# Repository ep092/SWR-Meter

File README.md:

# SWR-Meter
The goal is a SWR-Meter to analyse Antennas from 2,4GHz to 5,8GHz e.g. for FPV-Antennas.
The module ist based on a directional coupler and a power detector. 
A uC reads in the voltage with it's ADC and shows the results.

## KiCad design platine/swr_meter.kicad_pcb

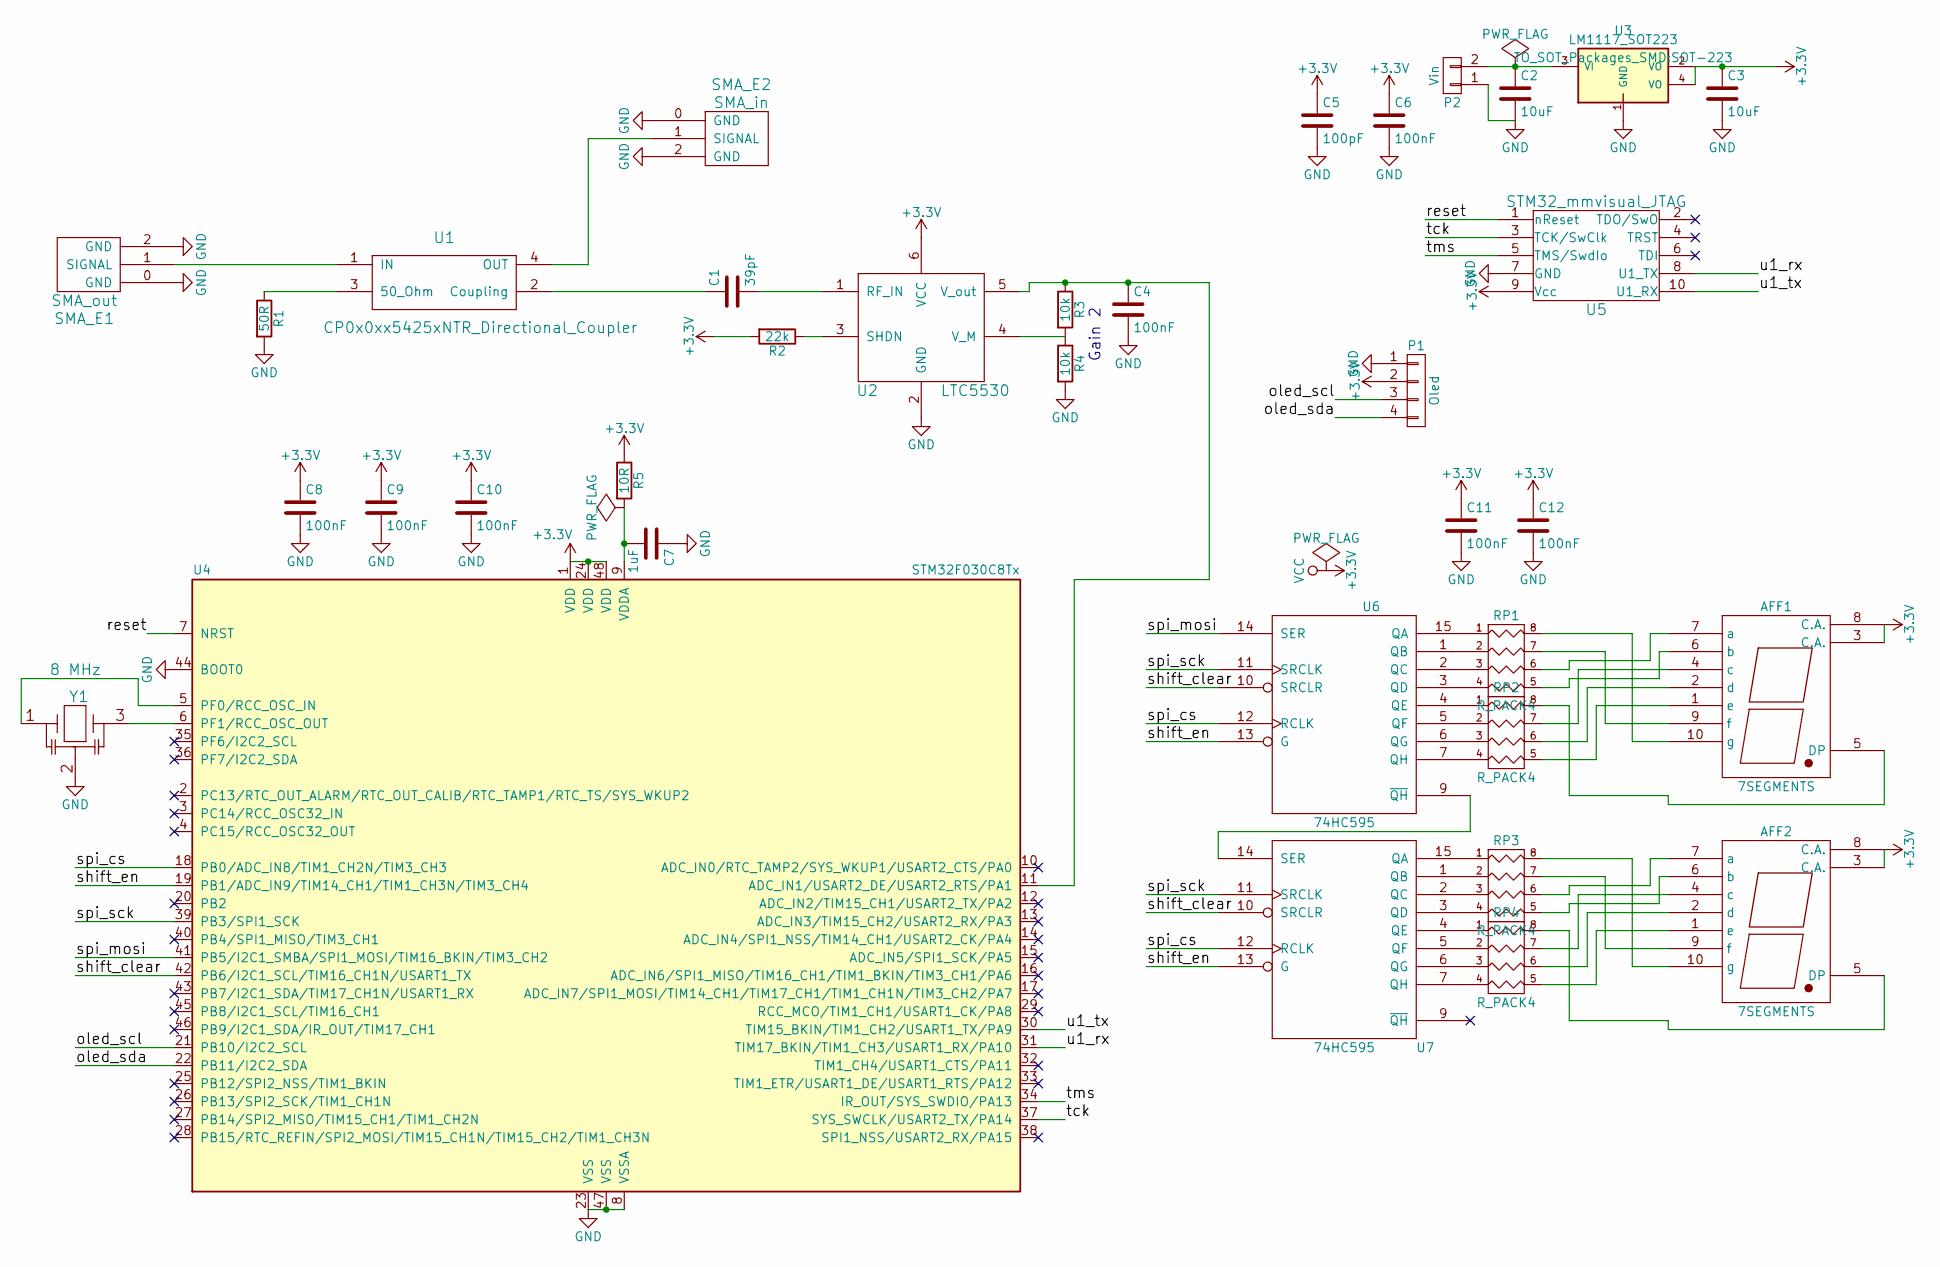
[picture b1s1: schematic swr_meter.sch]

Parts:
AFF1, AFF2: 7SEGMENTS; DIP-10_W7.62mm
C1: 39pF; C_0603
C2, C3: 10uF; R_0805
C4, C6, C8, C9, C10, C11, C12: 100nF; R_0402
C5: 100pF; C_0603
C7: 1uF; C_0603
P1: Oled; Pin_Header_Straight_1x04
P2: Vin; Pin_Header_Straight_1x02
R1: 50R; R_0603
R2: 22k; R_0603
R3, R4: 10k; R_0603
R5: 10R; C_0603
RP1, RP2, RP3, RP4: R_PACK4; R_array_4
SMA_E1: SMA_out; SMA_EDGE_Johnson_142-0701-801
SMA_E2: SMA_in; SMA_EDGE_Johnson_142-0701-801
U1: CP0x0xx5425xNTR_Directional_Coupler; CP0603_directional_coupler
U2: LTC5530; SOT-23-6
U3: LM1117_SOT223; SOT-223
U4: STM32F030C8Tx; LQFP-48_7x7mm_Pitch0.5mm
U5: STM32_mmvisual_JTAG; MICROMATCH-10
U6, U7: 74HC595; SOIC-16_3.9x9.9mm_Pitch1.27mm
Y1: 8 MHz; CerOsc_3,2x1,3

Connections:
+3V3: AFF1.3 (C.A.), AFF1.8 (C.A.), AFF2.3 (C.A.), AFF2.8 (C.A.), C3.1, C5.1, C6.1, C8.1, C9.1, C10.1, C11.1, C12.1, P1.2, R2.2, R5.1, U2.6 (VCC), U3.2 (VO), U3.4 (VO), U4.1 (VDD), U4.24 (VDD), U4.48 (VDD), U5.9 (Vcc), U6.16 (VCC), U7.16 (VCC); also elsewhere on the board
/oled_scl: P1.3, U4.21 (PB10/I2C2_SCL); also elsewhere on the board
/oled_sda: P1.4, U4.22 (PB11/I2C2_SDA); also elsewhere on the board
/reset: U4.7 (NRST), U5.1 (nReset)
/shift_clear: U4.42 (PB6/I2C1_SCL/TIM16_CH1N/USART1_TX), U6.10 (SRCLR), U7.10 (SRCLR)
/shift_en: U4.19 (PB1/ADC_IN9/TIM14_CH1/TIM1_CH3N/TIM3_CH4), U6.13 (G), U7.13 (G)
/spi_cs: U4.18 (PB0/ADC_IN8/TIM1_CH2N/TIM3_CH3), U6.12 (RCLK), U7.12 (RCLK)
/spi_mosi: U4.41 (PB5/I2C1_SMBA/SPI1_MOSI/TIM16_BKIN/TIM3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), U6.14 (SER)
/spi_sck: U4.39 (PB3/SPI1_SCK), U6.11 (SRCLK), U7.11 (SRCLK)
/tck: U4.37 (SYS_SWCLK/USART2_TX/PA14), U5.3 (TCK/SwClk)
/tms: U4.34 (IR_OUT/SYS_SWDIO/PA13), U5.5 (TMS/SwdIo)
/u1_rx: U4.31 (TIM17_BKIN/TIM1_CH3/USART1_RX/PA10), U5.8 (U1_TX)
/u1_tx: U4.30 (TIM15_BKIN/TIM1_CH2/USART1_TX/PA9), U5.10 (U1_RX)
GND: C2.2, C3.2, C4.2, C5.2, C6.2, C7.1, C8.2, C9.2, C10.2, C11.2, C12.2, P1.1, P2.1, R1.2, R4.2, SMA_E1.0 (GND), SMA_E1.2 (GND), SMA_E2.0 (GND), SMA_E2.2 (GND), U2.2 (GND), U3.1 (GND), U4.8 (VSSA), U4.23 (VSS), U4.44 (BOOT0), U4.47 (VSS), U5.7 (GND), U6.8 (GND), U7.8 (GND), Y1.2
unnamed: AFF1.1 (e), RP2.5 (R4)
unnamed: AFF1.2 (d), RP2.6 (R3)
unnamed: AFF1.4 (c), RP2.7 (R2)
unnamed: AFF1.5 (DP), RP2.8 (R1)
unnamed: AFF1.6 (b), RP1.5 (R4)
unnamed: AFF1.7 (a), RP1.6 (R3)
unnamed: AFF1.9 (f), RP1.7 (R2)
unnamed: AFF1.10 (g), RP1.8 (R1)
unnamed: AFF2.1 (e), RP4.5 (R4)
unnamed: AFF2.2 (d), RP4.6 (R3)
unnamed: AFF2.4 (c), RP4.7 (R2)
unnamed: AFF2.5 (DP), RP4.8 (R1)
unnamed: AFF2.6 (b), RP3.5 (R4)
unnamed: AFF2.7 (a), RP3.6 (R3)
unnamed: AFF2.9 (f), RP3.7 (R2)
unnamed: AFF2.10 (g), RP3.8 (R1)
unnamed: C1.1, U1.2 (Coupling)
unnamed: C1.2, U2.1 (RF_IN)
unnamed: C2.1, P2.2, U3.3 (VI)
unnamed: C4.1, R3.1, U2.5 (V_out), U4.11 (ADC_IN1/USART2_DE/USART2_RTS/PA1)
unnamed: C7.2, R5.2, U4.9 (VDDA)
unnamed: R1.1, U1.3 (50_Ohm)
unnamed: R2.1, U2.3 (SHDN)
unnamed: R3.2, R4.1, U2.4 (V_M)
unnamed: RP1.1, U6.15 (QA)
unnamed: RP1.2, U6.1 (QB)
unnamed: RP1.3, U6.2 (QC)
unnamed: RP1.4, U6.3 (QD)
unnamed: RP2.1, U6.4 (QE)
unnamed: RP2.2, U6.5 (QF)
unnamed: RP2.3, U6.6 (QG)
unnamed: RP2.4, U6.7 (QH)
unnamed: RP3.1, U7.15 (QA)
unnamed: RP3.2, U7.1 (QB)
unnamed: RP3.3, U7.2 (QC)
unnamed: RP3.4, U7.3 (QD)
unnamed: RP4.1, U7.4 (QE)
unnamed: RP4.2, U7.5 (QF)
unnamed: RP4.3, U7.6 (QG)
unnamed: RP4.4, U7.7 (QH)
unnamed: SMA_E1.1 (SIGNAL), U1.1 (IN)
unnamed: SMA_E2.1 (SIGNAL), U1.4 (OUT)
unnamed: U4.5 (PF0/RCC_OSC_IN), Y1.1
unnamed: U4.6 (PF1/RCC_OSC_OUT), Y1.3
unnamed: U6.9 (~QH), U7.14 (SER)

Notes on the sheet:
Gain 2

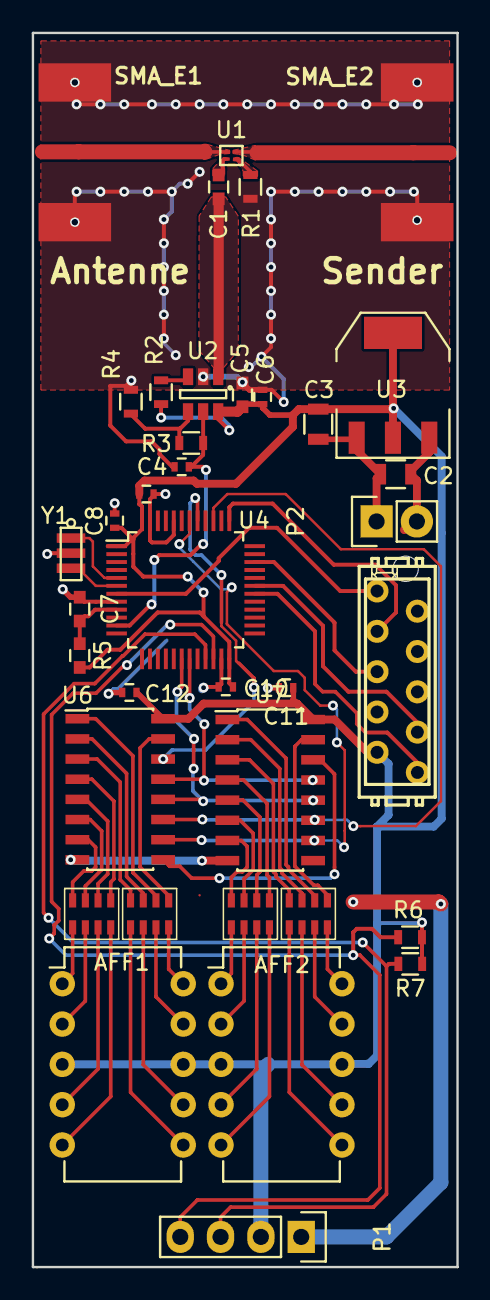
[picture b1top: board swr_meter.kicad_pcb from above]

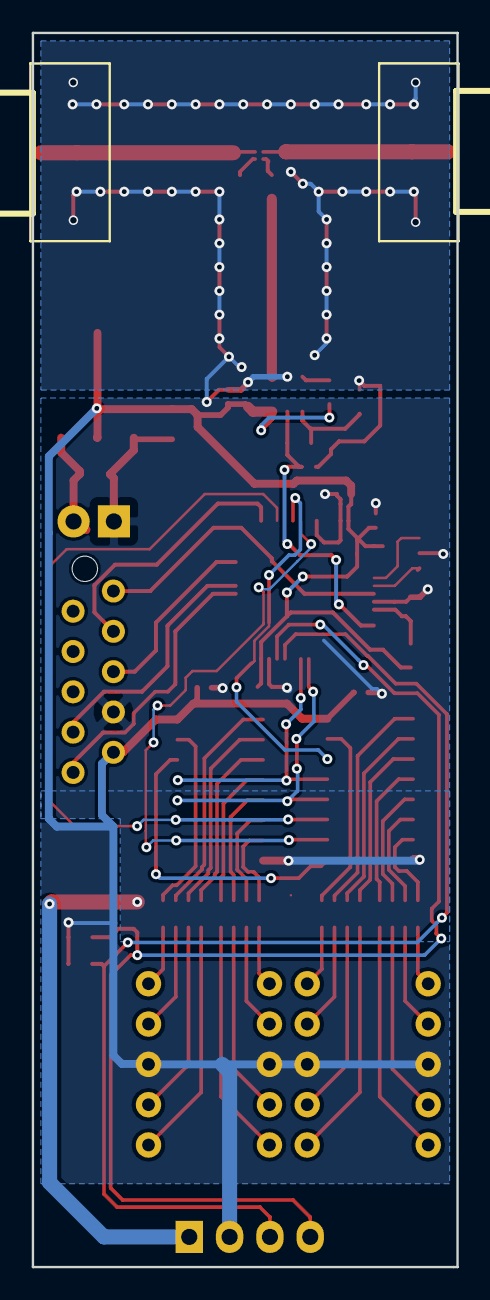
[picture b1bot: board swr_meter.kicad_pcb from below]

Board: 2 copper layers, 26.8 x 77.8 mm, 37 parts (2 on the bottom side), 59 nets.

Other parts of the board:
R6, R7: 3,3k; R_0603

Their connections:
+3V3: R6.1, R7.1; also elsewhere on the board
/oled_scl: R7.2; also elsewhere on the board
/oled_sda: R6.2; also elsewhere on the board

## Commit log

2016-04-11 inital commit of Readme
2016-04-11 initial commit of kicad files
2016-04-11 erste benötigte Bauteile angelegt und zu Schalplan hinzugefügt
2016-04-12 added parttypes
2016-04-12 added new power detector
2016-04-12 changed back to lt power detector because of bad input impedance of the ti power detector (page 10 figure 7 of LMH2110 datasheet)
2016-04-15 worked on schematic and started pcb
2016-04-15 changed sma signal pads
2016-04-15 HF Leiterbahnbreiten überarbeitet. HF-Teil fertig
2016-04-15 wiring of stm32
2016-04-15 routing of stm32
2016-04-15 moved micromatch. finished except oled an seven-segment display
2016-04-15 aligned text on silkscreen
2016-04-15 Datenblätter für 7-segmentanzeigen und OLED-Treiber hinzugefügt
2016-04-15 added one 7-segment display
2016-04-15 work on 7-segment display
2016-04-15 7segments angeschlossen und resonator berichtigt
2016-04-15 schematic complete, pcb complete, drc ok
2016-04-15 i2c pullups added; outline added
2016-04-16 perhaps not correctly saved bevore the last commit.
2016-04-16 gerberfiles dazugefügt und auf der Platine einen kleinen Text geschrieben.
2016-04-18 changed minimal isolation distance to 160um
